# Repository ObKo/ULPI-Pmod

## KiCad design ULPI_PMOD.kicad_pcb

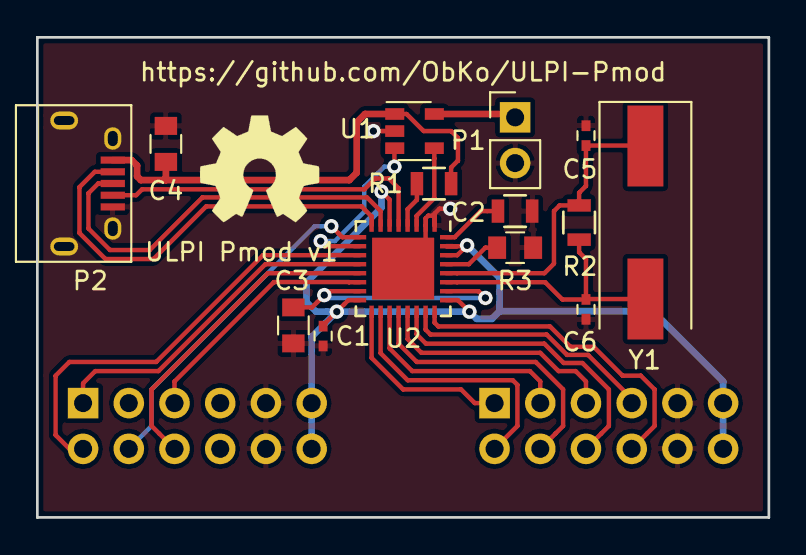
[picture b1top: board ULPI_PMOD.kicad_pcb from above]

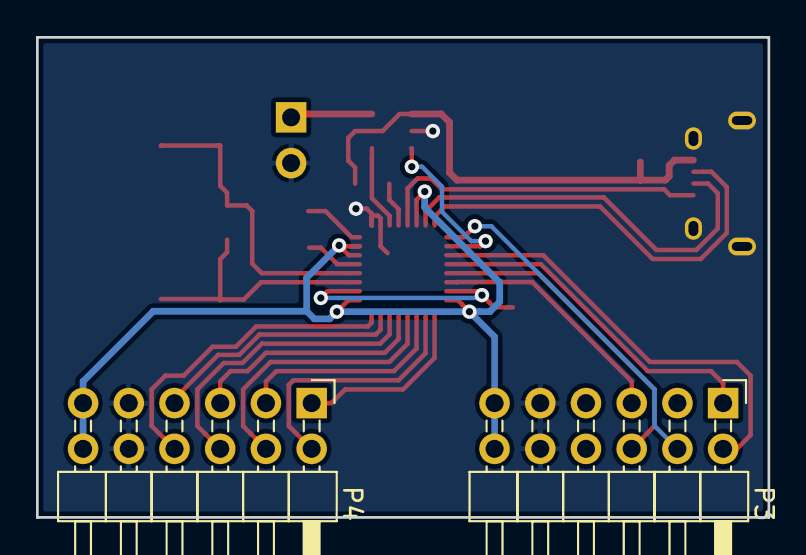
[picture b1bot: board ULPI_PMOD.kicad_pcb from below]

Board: 2 copper layers, 40.6 x 26.7 mm, 16 parts (2 on the bottom side), 28 nets.

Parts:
C1: 100nF; C_0402
C2, C3, C4: 4.7μF; C_0805
C5, C6: 22pF; C_0402
P1: CONN_01X02; Pin_Header_Straight_1x02_Pitch2.54mm
P2: USB_OTG; USB_Micro-B
P3: JB; Pin_Header_Angled_2x06_Pitch2.54mm
P4: JC; Pin_Header_Angled_2x06_Pitch2.54mm
R1: 820; R_0805
R2: 1M; R_0805
R3: 12k; R_0805
U1: STMPS2141; SOT-23-5
U2: USB3300; QFN-32-1EP_5x5mm_Pitch0.5mm
Y1: Crystal; Crystal_SMD_HC49-SD

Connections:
+3V3: C1.1, P3.11, P3.12, P4.11, P4.12, U2.6, U2.16, U2.25, U2.30, U2.31
+5V: P1.1, U1.5
/CPEN: U1.4, U2.3
/D+: P2.3, U2.7
/D-: P2.2, U2.8
/EXTVBUS: U1.3, U2.10
/ULPI_CLK: P3.5, U2.14
/ULPI_DATA0: P4.8, U2.24
/ULPI_DATA1: P4.7, U2.23
/ULPI_DATA2: P4.6, U2.22
/ULPI_DATA3: P4.5, U2.21
/ULPI_DATA4: P4.4, U2.20
/ULPI_DATA5: P4.3, U2.19
/ULPI_DATA6: P4.2, U2.18
/ULPI_DATA7: P4.1, U2.17
/ULPI_DIR: P3.1, U2.12
/ULPI_NXT: P3.2, U2.11
/ULPI_RESET: P3.4, U2.9
/ULPI_STP: P3.6, U2.13
GND: C1.2, C2.2, C3.2, C4.2, C5.2, C6.2, P1.2, P2.5, P2.6, P3.9, P3.10, P4.9, P4.10, R3.2, U1.2, U2.1, U2.2, U2.33
unnamed: C2.1, U2.29
unnamed: C3.1, U2.15, U2.26
unnamed: C4.1, P2.1, R1.2, U1.1
unnamed: C5.1, R2.2, U2.28, Y1.1
unnamed: C6.1, R2.1, U2.27, Y1.2
unnamed: P2.4, U2.5
unnamed: R1.1, U2.4
unnamed: R3.1, U2.32

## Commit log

2017-01-24 Initial commit.
2017-01-25 PCB done.
2017-01-27 Final PCB.
2017-01-27 ULPI_PMOD -> ULPI-Pmod.
2017-01-27 Licence (CERN Open Hardware Licence).
